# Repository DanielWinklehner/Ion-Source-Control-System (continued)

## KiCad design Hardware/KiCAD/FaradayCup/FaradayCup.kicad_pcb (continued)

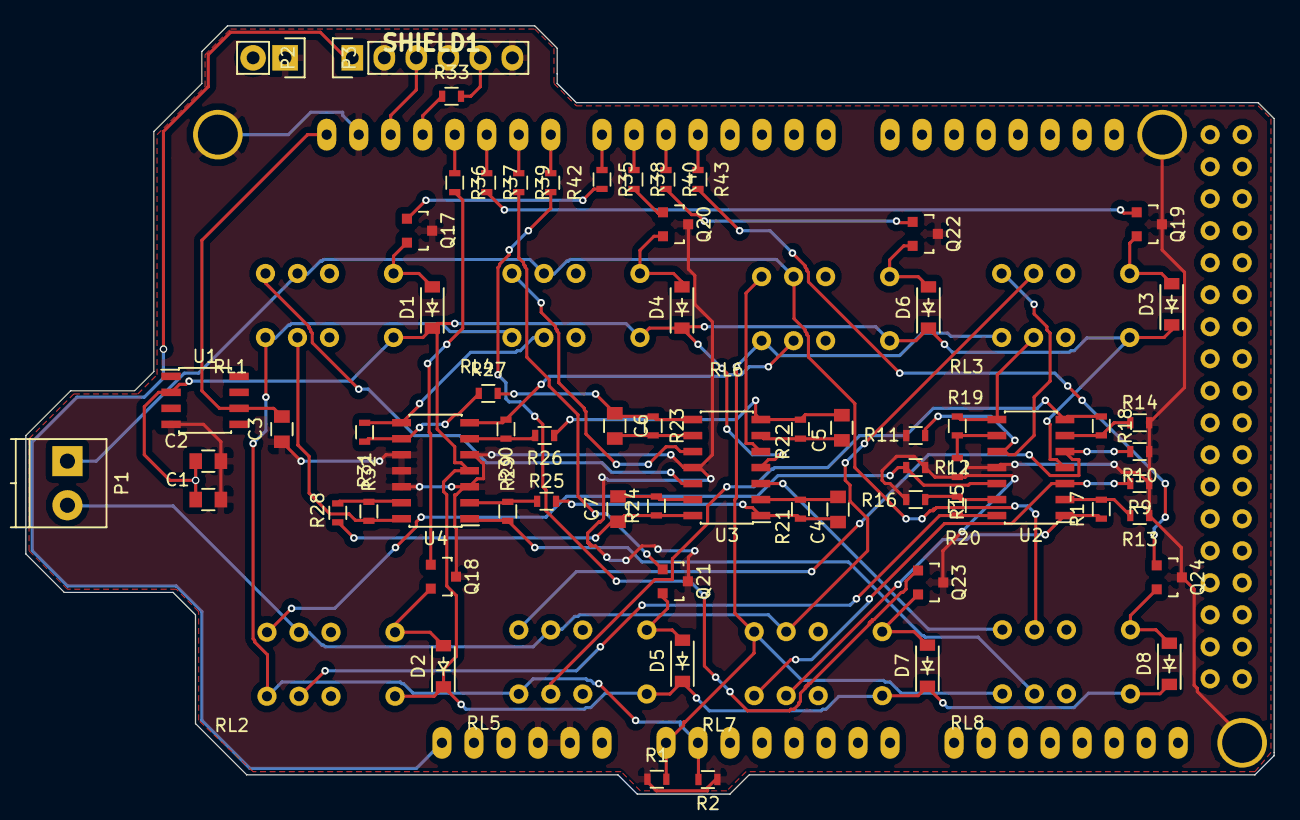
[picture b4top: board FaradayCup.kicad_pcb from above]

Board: 2 copper layers, 99.1 x 61.0 mm, 74 parts (0 on the bottom side), 67 nets.

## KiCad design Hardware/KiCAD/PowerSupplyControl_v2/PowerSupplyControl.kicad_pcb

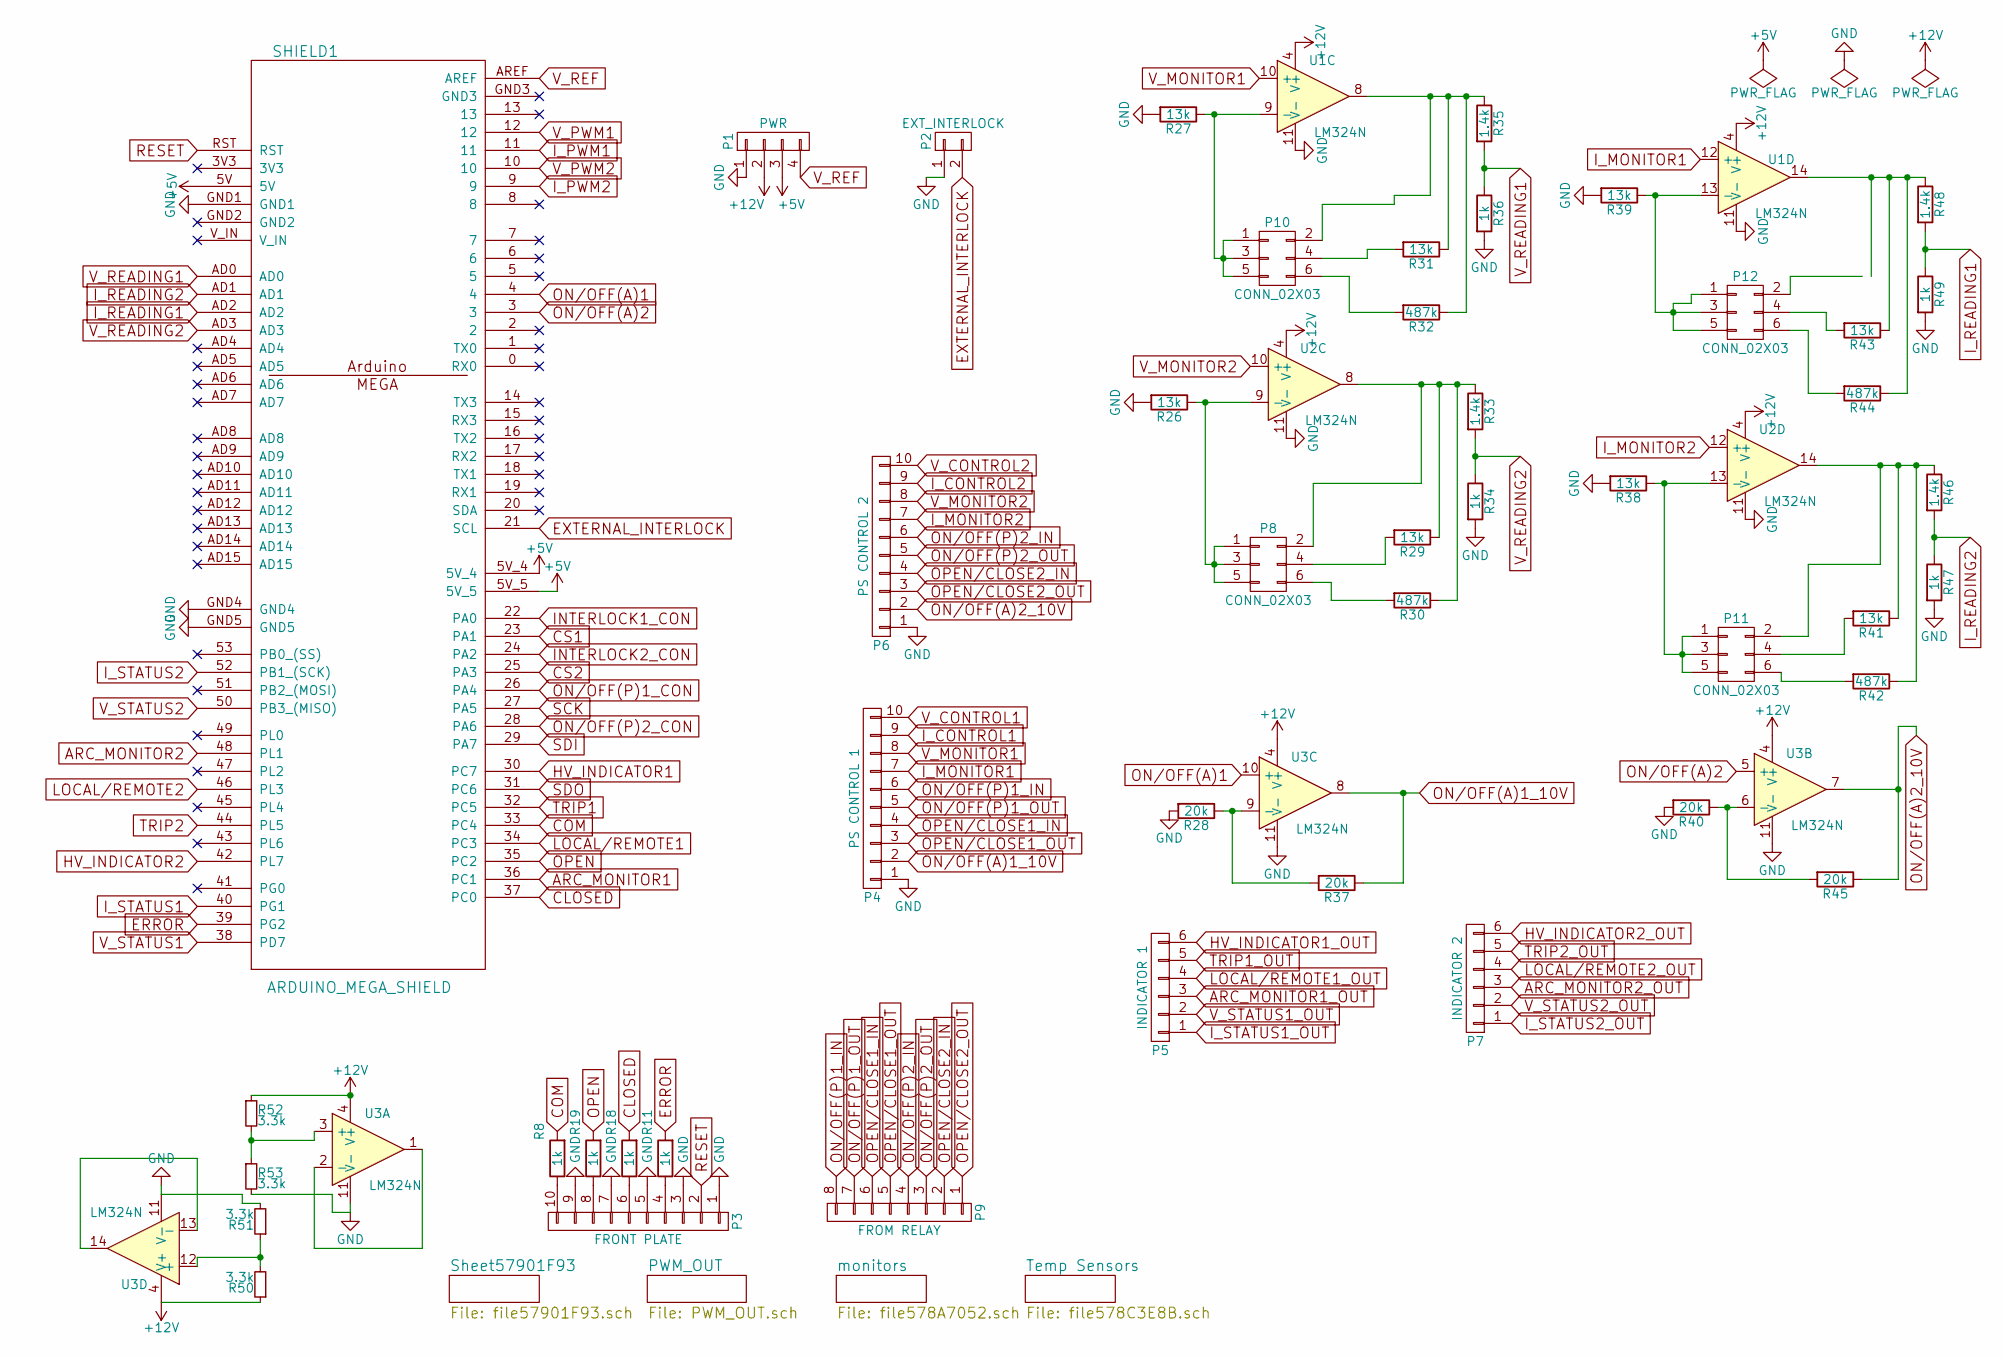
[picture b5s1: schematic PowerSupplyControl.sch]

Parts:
P1: PWR; Pin_Header_Straight_1x04
P2: EXT_INTERLOCK; TerminalBlock_Pheonix_PT-3.5mm_2pol
P3: FRONT PLATE; TerminalBlock_Pheonix_PT-3.5mm_10pol
P4: PS CONTROL 1; TerminalBlock_Pheonix_PT-3.5mm_10pol
P5: INDICATOR 1; Pin_Header_Straight_1x06
P6: PS CONTROL 2; TerminalBlock_Pheonix_PT-3.5mm_10pol
P7: INDICATOR 2; Pin_Header_Straight_1x06
P8, P10, P11, P12: CONN_02X03; Pin_Header_Straight_2x03
P9: FROM RELAY; Pin_Header_Straight_1x08
R8, R11, R18, R19, R34, R36, R47, R49: 1k; R_0603
R26, R27, R29, R31, R38, R39, R41, R43: 13k; R_0603
R28, R37, R40, R45: 20k; R_0603
R30, R32, R42, R44: 487k; R_0805
R33, R35, R46, R48: 1.4k; R_0603
R50, R51, R52, R53: 3.3k; R_0603
SHIELD1: ARDUINO_MEGA_SHIELD
U1, U2, U3: LM324N; SOIC-14_N

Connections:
+5V: P1.3, SHIELD1.5V, SHIELD1.5V_4, SHIELD1.5V_5; also elsewhere on the board
+12V: P1.2, R50.1, R52.1, U1.4 (V+), U2.4 (V+), U3.4 (V+)
ARC_MONITOR1: SHIELD1.36 (PC1); also elsewhere on the board
ARC_MONITOR1_OUT: P5.3; also elsewhere on the board
ARC_MONITOR2: SHIELD1.48 (PL1); also elsewhere on the board
ARC_MONITOR2_OUT: P7.3; also elsewhere on the board
CLOSED: R18.2, SHIELD1.37 (PC0)
COM: R8.2, SHIELD1.33 (PC4)
CS1: SHIELD1.23 (PA1); also elsewhere on the board
CS2: SHIELD1.25 (PA3); also elsewhere on the board
ERROR: R11.2, SHIELD1.39 (PG2)
EXTERNAL_INTERLOCK: P2.2, SHIELD1.21 (SCL)
GND: P1.1, P2.1, P3.1, P3.3, P3.5, P3.7, P3.9, P4.1, P6.1, R26.2, R27.2, R28.2, R34.2, R36.2, R38.2, R39.2, R40.2, R47.2, R49.2, R51.2, R53.2, SHIELD1.GND1, SHIELD1.GND4, SHIELD1.GND5, U1.11 (V-), U2.11 (V-), U3.11 (V-); also elsewhere on the board
HV_INDICATOR1: SHIELD1.30 (PC7); also elsewhere on the board
HV_INDICATOR1_OUT: P5.6; also elsewhere on the board
HV_INDICATOR2: SHIELD1.42 (PL7); also elsewhere on the board
HV_INDICATOR2_OUT: P7.6; also elsewhere on the board
INTERLOCK1_CON: SHIELD1.22 (PA0)
INTERLOCK2_CON: SHIELD1.24 (PA2)
I_CONTROL1: P4.9; also elsewhere on the board
I_CONTROL2: P6.9; also elsewhere on the board
I_MONITOR1: P4.7, U1.12 (+)
I_MONITOR2: P6.7, U2.12 (+)
I_PWM1: SHIELD1.11; also elsewhere on the board
I_PWM2: SHIELD1.9; also elsewhere on the board
I_READING1: R48.2, R49.1, SHIELD1.AD2
I_READING2: R46.2, R47.1, SHIELD1.AD1
I_STATUS1: SHIELD1.40 (PG1); also elsewhere on the board
I_STATUS1_OUT: P5.1; also elsewhere on the board
I_STATUS2: SHIELD1.52 (PB1_(SCK)); also elsewhere on the board
I_STATUS2_OUT: P7.1; also elsewhere on the board
LOCAL/REMOTE1: SHIELD1.34 (PC3); also elsewhere on the board
LOCAL/REMOTE1_OUT: P5.4; also elsewhere on the board
LOCAL/REMOTE2: SHIELD1.46 (PL3); also elsewhere on the board
LOCAL/REMOTE2_OUT: P7.4; also elsewhere on the board
unnamed: P3.4, R11.1
unnamed: P3.6, R18.1
unnamed: P3.8, R19.1
unnamed: P3.10, R8.1
unnamed: P8.1, P8.3, P8.5, R26.1, U2.9 (-)
unnamed: P8.2, R29.1, R30.1, R33.1, U2.8
unnamed: P8.4, R29.2
unnamed: P8.6, R30.2
unnamed: P10.1, P10.3, P10.5, R27.1, U1.9 (-)
unnamed: P10.2, R31.1, R32.1, R35.1, U1.8
unnamed: P10.4, R31.2
unnamed: P10.6, R32.2
unnamed: P11.1, P11.3, P11.5, R38.1, U2.13 (-)
unnamed: P11.2, R41.1, R42.1, R46.1, U2.14
unnamed: P11.4, R41.2
unnamed: P11.6, R42.2
unnamed: P12.1, P12.3, P12.5, R39.1, U1.13 (-)
unnamed: P12.4, R43.2
unnamed: P12.6, R44.2
unnamed: R28.1, R37.2, U3.9 (-)
unnamed: R40.1, R45.2, U3.6 (-)
unnamed: R43.1, R44.1, R48.1, U1.14
unnamed: R50.2, R51.1, U3.12 (+)
unnamed: R52.2, R53.1, U3.3 (+)
unnamed: U3.1, U3.2 (-)
unnamed: U3.13 (-), U3.14
ON/OFF(A)1: SHIELD1.4, U3.10 (+)
ON/OFF(A)1_10V: P4.2, R37.1, U3.8
ON/OFF(A)2: SHIELD1.3, U3.5 (+)
ON/OFF(A)2_10V: P6.2, R45.1, U3.7
ON/OFF(P)1_CON: SHIELD1.26 (PA4)
ON/OFF(P)1_IN: P4.6, P9.8
ON/OFF(P)1_OUT: P4.5, P9.7
ON/OFF(P)2_CON: SHIELD1.28 (PA6)
ON/OFF(P)2_IN: P6.6, P9.4
ON/OFF(P)2_OUT: P6.5, P9.3
OPEN: R19.2, SHIELD1.35 (PC2)
OPEN/CLOSE1_IN: P4.4, P9.6
OPEN/CLOSE1_OUT: P4.3, P9.5
OPEN/CLOSE2_IN: P6.4, P9.2
OPEN/CLOSE2_OUT: P6.3, P9.1
RESET: P3.2, SHIELD1.RST
SCK: SHIELD1.27 (PA5); also elsewhere on the board
SDI: SHIELD1.29 (PA7); also elsewhere on the board
SDO: SHIELD1.31 (PC6); also elsewhere on the board
TRIP1: SHIELD1.32 (PC5); also elsewhere on the board
TRIP1_OUT: P5.5; also elsewhere on the board
TRIP2: SHIELD1.44 (PL5); also elsewhere on the board
TRIP2_OUT: P7.5; also elsewhere on the board
V_CONTROL1: P4.10; also elsewhere on the board
V_CONTROL2: P6.10; also elsewhere on the board
V_MONITOR1: P4.8, U1.10 (+)
V_MONITOR2: P6.8, U2.10 (+)
V_PWM1: SHIELD1.12; also elsewhere on the board
V_PWM2: SHIELD1.10; also elsewhere on the board
V_READING1: R35.2, R36.1, SHIELD1.AD0
V_READING2: R33.2, R34.1, SHIELD1.AD3
V_REF: P1.4, SHIELD1.AREF; also elsewhere on the board
V_STATUS1: SHIELD1.38 (PD7); also elsewhere on the board
V_STATUS1_OUT: P5.2; also elsewhere on the board
V_STATUS2: SHIELD1.50 (PB3_(MISO)); also elsewhere on the board
V_STATUS2_OUT: P7.2; also elsewhere on the board

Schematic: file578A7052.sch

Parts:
R54, R55, R56, R57, R58, R59, R60, R61, R62, R63, R64, R65, R66, R67, R68, R69, R70, R71, R72, R73, R74, R75, R76, R77: 1k; R_0603

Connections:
ARC_MONITOR1: R57.1, R69.2; also elsewhere on the board
ARC_MONITOR1_OUT: R57.2; also elsewhere on the board
ARC_MONITOR2: R63.1, R75.2; also elsewhere on the board
ARC_MONITOR2_OUT: R63.2; also elsewhere on the board
GND: R66.1, R67.1, R68.1, R69.1, R70.1, R71.1, R72.1, R73.1, R74.1, R75.1, R76.1, R77.1; also elsewhere on the board
HV_INDICATOR1: R54.1, R66.2; also elsewhere on the board
HV_INDICATOR1_OUT: R54.2; also elsewhere on the board
HV_INDICATOR2: R60.1, R72.2; also elsewhere on the board
HV_INDICATOR2_OUT: R60.2; also elsewhere on the board
I_STATUS1: R59.1, R71.2; also elsewhere on the board
I_STATUS1_OUT: R59.2; also elsewhere on the board
I_STATUS2: R65.1, R77.2; also elsewhere on the board
I_STATUS2_OUT: R65.2; also elsewhere on the board
LOCAL/REMOTE1: R56.1, R68.2; also elsewhere on the board
LOCAL/REMOTE1_OUT: R56.2; also elsewhere on the board
LOCAL/REMOTE2: R62.1, R74.2; also elsewhere on the board
LOCAL/REMOTE2_OUT: R62.2; also elsewhere on the board
TRIP1: R55.1, R67.2; also elsewhere on the board
TRIP1_OUT: R55.2; also elsewhere on the board
TRIP2: R61.1, R73.2; also elsewhere on the board
TRIP2_OUT: R61.2; also elsewhere on the board
V_STATUS1: R58.1, R70.2; also elsewhere on the board
V_STATUS1_OUT: R58.2; also elsewhere on the board
V_STATUS2: R64.1, R76.2; also elsewhere on the board
V_STATUS2_OUT: R64.2; also elsewhere on the board

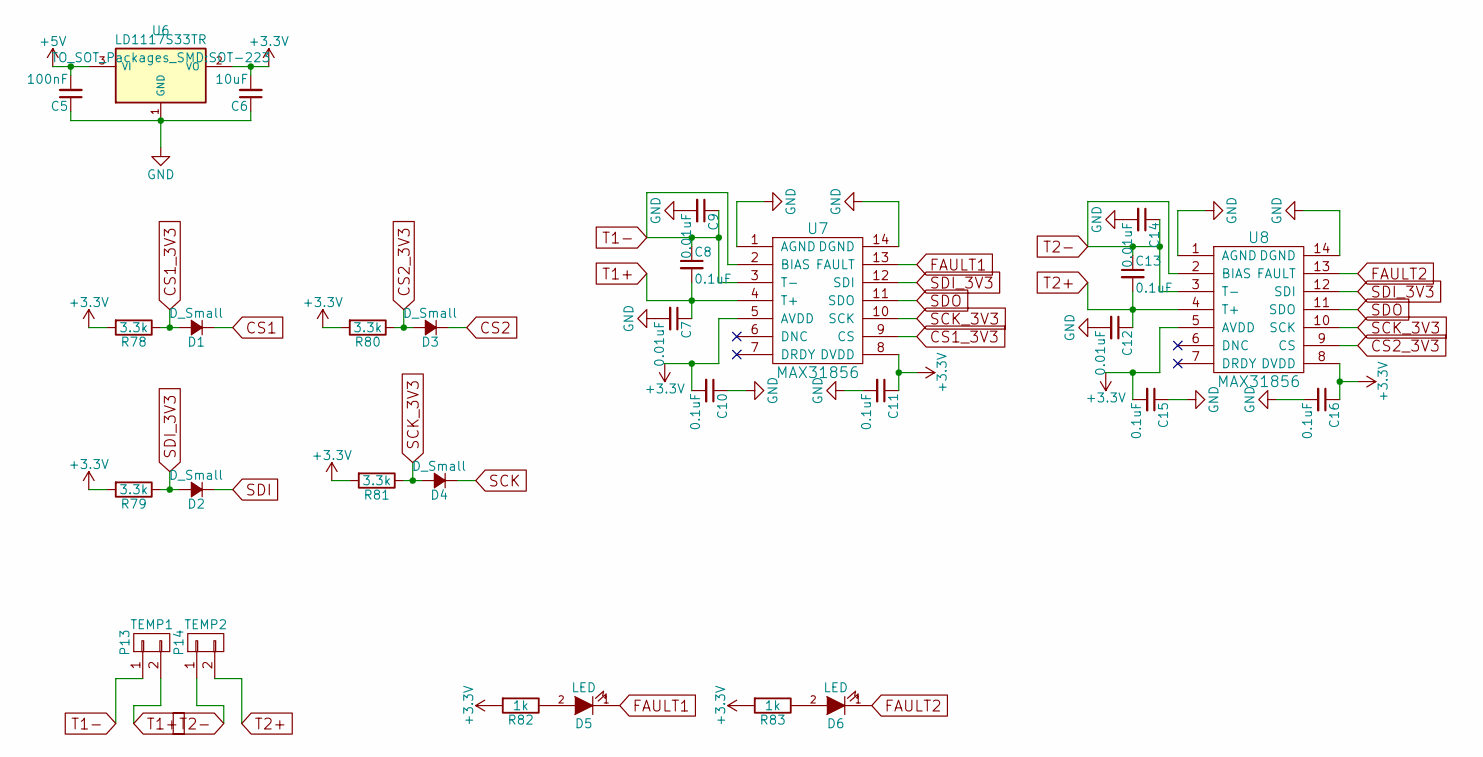
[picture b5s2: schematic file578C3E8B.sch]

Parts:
C5: 100nF; C_0805
C6: 10uF; C_0805
C7, C9, C12, C14: 0.01uF; C_0805
C8, C10, C11, C13, C15, C16: 0.1uF; C_0805
D1, D2, D3, D4: D_Small; SOD-323
D5, D6: LED; LED-3MM
P13: TEMP1; TerminalBlock_Pheonix_PT-3.5mm_2pol
P14: TEMP2; TerminalBlock_Pheonix_PT-3.5mm_2pol
R78, R79, R80, R81: 3.3k; R_0603
R82, R83: 1k; R_0603
U6: LD1117S33TR; SOT-223
U7, U8: MAX31856; TSSOP-14_4.4x5mm_Pitch0.65mm

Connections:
+3V3: C6.2, C10.2, C11.1, C15.2, C16.1, R78.2, R79.2, R80.2, R81.2, R82.2, R83.2, U6.2 (VO), U7.5 (AVDD), U7.8 (DVDD), U8.5 (AVDD), U8.8 (DVDD)
+5V: C5.2, U6.3 (VI); also elsewhere on the board
CS1: D1.1 (K); also elsewhere on the board
CS1_3V3: D1.2 (A), R78.1, U7.9 (CS)
CS2: D3.1 (K); also elsewhere on the board
CS2_3V3: D3.2 (A), R80.1, U8.9 (CS)
FAULT1: D5.1 (K), U7.13 (FAULT)
FAULT2: D6.1 (K), U8.13 (FAULT)
GND: C5.1, C6.1, C7.2, C9.2, C10.1, C11.2, C12.2, C14.2, C15.1, C16.2, U6.1 (GND), U7.1 (AGND), U7.14 (DGND), U8.1 (AGND), U8.14 (DGND); also elsewhere on the board
unnamed: D5.2 (A), R82.1
unnamed: D6.2 (A), R83.1
SCK: D4.1 (K); also elsewhere on the board
SCK_3V3: D4.2 (A), R81.1, U7.10 (SCK), U8.10 (SCK)
SDI: D2.1 (K); also elsewhere on the board
SDI_3V3: D2.2 (A), R79.1, U7.12 (SDI), U8.12 (SDI)
SDO: U7.11 (SDO), U8.11 (SDO); also elsewhere on the board
T1+: C7.1, C8.2, P13.2, U7.4 (T+)
T1-: C8.1, C9.1, P13.1, U7.2 (BIAS), U7.3 (T-)
T2+: C12.1, C13.2, P14.2, U8.4 (T+)
T2-: C13.1, C14.1, P14.1, U8.2 (BIAS), U8.3 (T-)

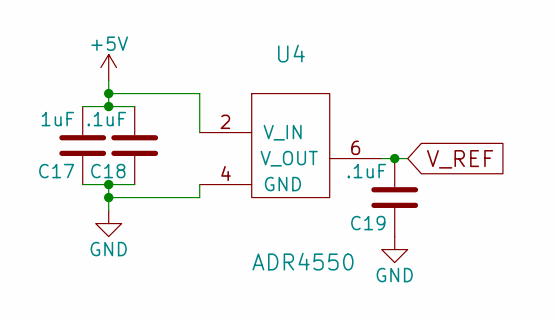
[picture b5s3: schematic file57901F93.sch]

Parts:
C17: 1uF; C_0805
C18, C19: .1uF; C_0805
U4: ADR4550; SOIC-8_3.9x4.9mm_Pitch1.27mm

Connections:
+5V: C17.2, C18.2, U4.2 (V_IN); also elsewhere on the board
GND: C17.1, C18.1, C19.1, U4.4 (GND); also elsewhere on the board
V_REF: C19.2, U4.6 (V_OUT); also elsewhere on the board

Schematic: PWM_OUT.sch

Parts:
C1, C2, C3, C4: 47uF; C_1210
R1, R2, R3, R4: 10k; R_0603
R6, R10, R12, R15, R16, R21, R22, R24: 20k; R_0603
R7, R9, R13, R14, R17, R20, R23, R25: 1k; R_0603
SW1, SW2, SW3, SW4: SPST; SW_DIP_x1_Slide
U1, U2: LM324N; SOIC-14_N

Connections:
+12V: U1.4 (V+), U2.4 (V+); also elsewhere on the board
GND: C1.2, C2.2, C3.2, C4.2, R6.1, R7.2, R14.2, R15.1, R16.1, R17.2, R24.1, R25.2, U1.11 (V-), U2.11 (V-); also elsewhere on the board
I_CONTROL1: R20.1, SW3.1; also elsewhere on the board
I_CONTROL2: R9.1, SW1.1; also elsewhere on the board
I_OUT1: C3.1, R3.1, U1.5 (+)
I_OUT2: C1.1, R1.1, U2.5 (+)
I_PWM1: R3.2; also elsewhere on the board
I_PWM2: R1.2; also elsewhere on the board
unnamed: R7.1, SW1.2
unnamed: R14.1, SW2.2
unnamed: R17.1, SW3.2
unnamed: R25.1, SW4.2
V_CONTROL1: R23.1, SW4.1; also elsewhere on the board
V_CONTROL2: R13.1, SW2.1; also elsewhere on the board
V_OUT1: C2.1, R2.1, U1.3 (+)
V_OUT2: C4.1, R4.1, U2.3 (+)
V_PWM1: R2.2; also elsewhere on the board
V_PWM2: R4.2; also elsewhere on the board

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
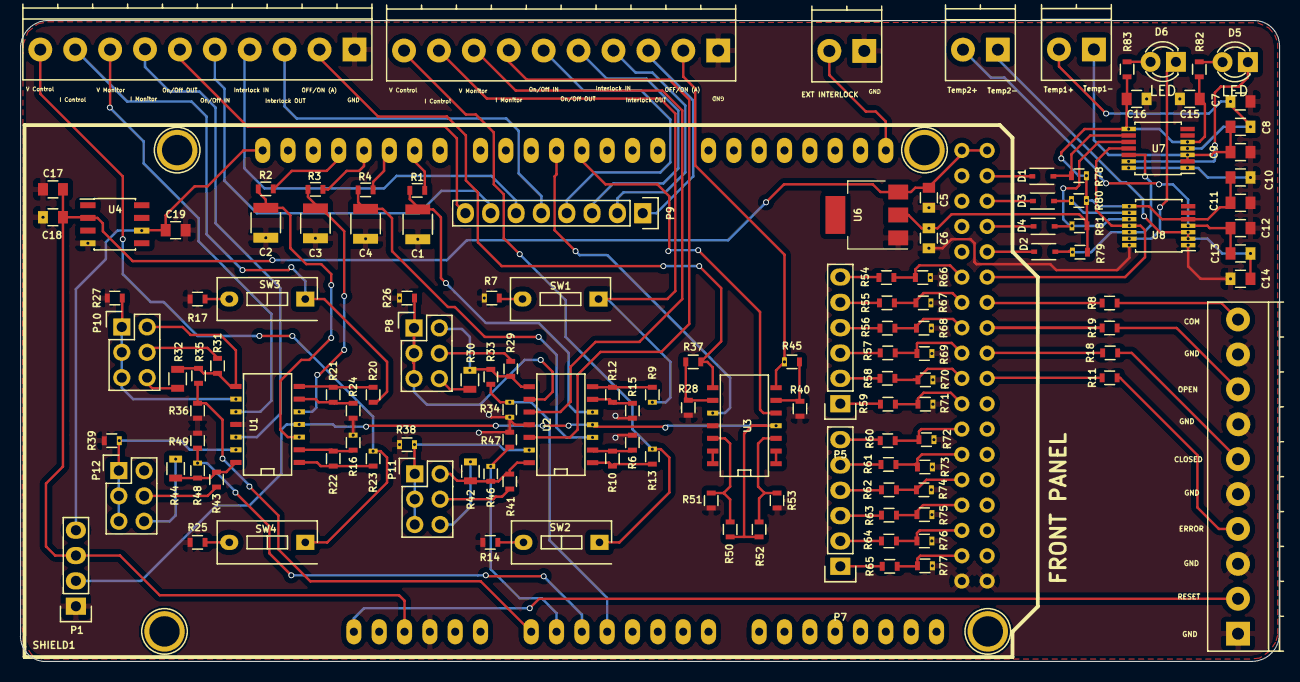
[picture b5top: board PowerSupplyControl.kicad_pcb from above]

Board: 2 copper layers, 126.2 x 64.3 mm, 133 parts (0 on the bottom side), 122 nets.

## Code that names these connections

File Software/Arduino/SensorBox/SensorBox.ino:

#include <Channel.h>
#include <Communication.h>

// Set up serial communication
char inputMessage[128];
mist1::Communication com = mist1::Communication("Sensor Box");

#include <MAX31856.h>

// Flow meters. x5.
const int flowSensorPins[] = {18, 19, 20, 3, 2};
volatile int flowSensorFreqs[] = {0, 0, 0, 0, 0};
float flowSensorFreqsWrite[] = {0.0, 0.0, 0.0, 0.0, 0.0};
unsigned long currentTime;
unsigned long cloopTime;

// Temperature Sensors. 8x.
// The power requirement for the board is less than 2mA.  Most microcontrollers can source or sink a lot more
// than that one each I/O pin.  For example, the ATmega328 supports up to 20mA.  So it is possible to power the
// board using I/O pins for power - so you can turn the board on and off (if you want to).
// FAULT and DRDY are not used by the library (see above)
#define SCK1    44
#define SDI1    42
#define SDO1    40

#define SCK2    49
#define SDI2    51
#define SDO2    53

#define CS1    46
#define CS2    48
#define CS3    50
#define CS4    52
#define CS5    47
#define CS6    45
#define CS7    43
#define CS8    41

// Define pins for error state LED, communication LED
#define LED_ERR 12
#define LED_COM 13

// MAX31856 Initial settings (see MAX31856.h and the MAX31856 datasheet)
// The default noise filter is 60Hz, suitable for the USA
#define CR0_INIT  (CR0_AUTOMATIC_CONVERSION + CR0_OPEN_CIRCUIT_FAULT_TYPE_K /* + CR0_NOISE_FILTER_50HZ */)
#define CR1_INIT  (CR1_AVERAGE_2_SAMPLES + CR1_THERMOCOUPLE_TYPE_K)
#define MASK_INIT (~(MASK_VOLTAGE_UNDER_OVER_FAULT + MASK_THERMOCOUPLE_OPEN_FAULT))

MAX31856 *temperature1;
MAX31856 *temperature2;
MAX31856 *temperature3;
MAX31856 *temperature4;
MAX31856 *temperature5;
MAX31856 *temperature6;
MAX31856 *temperature7;
//MAX31856 *temperature8;

float t[] = {0.0, 0.0, 0.0, 0.0, 0.0, 0.0, 0.0, 0.0};


float get_t1(){
  return t[0];
}

float get_t2(){
  return t[1];
}

float get_t3(){
  return t[2];
}

float get_t4(){
  return t[3];
}

float get_t5(){
  return t[4];
}

float get_t6(){
  return t[5];
}

float get_t7(){
  return t[6];
}

float get_flow1(){
  return flowSensorFreqsWrite[0];
}

float get_flow2(){
  return flowSensorFreqsWrite[1];
}

float get_flow3(){
  return flowSensorFreqsWrite[2];
}

float get_flow4(){
  return flowSensorFreqsWrite[3];
}

float get_flow5(){
  return flowSensorFreqsWrite[4];
}

void dummyFunc(float set_value){
  //Serial.println("Called the dummy function!");
}

void setup()   { 
  // Init Com and Error LED's
  pinMode(LED_ERR, OUTPUT);
  pinMode(LED_COM, OUTPUT);
  digitalWrite(LED_COM, LOW);
  digitalWrite(LED_ERR, LOW);
  
  // Flow Meters.
  for (unsigned i = 0; i < sizeof(flowSensorPins) / sizeof(int); i++) {
    pinMode(flowSensorPins[i], INPUT);
    // Activate the pullup resistor
    digitalWrite(flowSensorPins[i], HIGH);
  }

  Serial.begin(115200); // 115200

  // Interrupts for flow sensors.
  attachInterrupt(digitalPinToInterrupt(flowSensorPins[0]), flow_interrupt0, RISING);
  attachInterrupt(digitalPinToInterrupt(flowSensorPins[1]), flow_interrupt1, RISING);
  attachInterrupt(digitalPinToInterrupt(flowSensorPins[2]), flow_interrupt2, RISING);
  attachInterrupt(digitalPinToInterrupt(flowSensorPins[3]), flow_interrupt3, RISING);
  attachInterrupt(digitalPinToInterrupt(flowSensorPins[4]), flow_interrupt4, RISING);

  // Define the pins used to communicate with the MAX31856
  temperature1 = new MAX31856(SDI1, SDO1, CS1, SCK1);
  temperature2 = new MAX31856(SDI1, SDO1, CS2, SCK1);
  temperature3 = new MAX31856(SDI1, SDO1, CS3, SCK1);
  temperature4 = new MAX31856(SDI1, SDO1, CS4, SCK1);
  temperature5 = new MAX31856(SDI2, SDO2, CS5, SCK2);
  temperature6 = new MAX31856(SDI2, SDO2, CS6, SCK2);
  temperature7 = new MAX31856(SDI2, SDO2, CS7, SCK2);
//  temperature8 = new MAX31856(SDI2, SDO2, CS8, SCK2);
  
  // Initializing the MAX31855's registers
  temperature1->writeRegister(REGISTER_CR0, CR0_INIT);
  temperature1->writeRegister(REGISTER_CR1, CR1_INIT);
  temperature1->writeRegister(REGISTER_MASK, MASK_INIT);

  temperature2->writeRegister(REGISTER_CR0, CR0_INIT);
  temperature2->writeRegister(REGISTER_CR1, CR1_INIT);
  temperature2->writeRegister(REGISTER_MASK, MASK_INIT);

  temperature3->writeRegister(REGISTER_CR0, CR0_INIT);
  temperature3->writeRegister(REGISTER_CR1, CR1_INIT);
  temperature3->writeRegister(REGISTER_MASK, MASK_INIT);

  temperature4->writeRegister(REGISTER_CR0, CR0_INIT);
  temperature4->writeRegister(REGISTER_CR1, CR1_INIT);
  temperature4->writeRegister(REGISTER_MASK, MASK_INIT);

  temperature5->writeRegister(REGISTER_CR0, CR0_INIT);
  temperature5->writeRegister(REGISTER_CR1, CR1_INIT);
  temperature5->writeRegister(REGISTER_MASK, MASK_INIT);

  temperature6->writeRegister(REGISTER_CR0, CR0_INIT);
  temperature6->writeRegister(REGISTER_CR1, CR1_INIT);
  temperature6->writeRegister(REGISTER_MASK, MASK_INIT);

  temperature7->writeRegister(REGISTER_CR0, CR0_INIT);
  temperature7->writeRegister(REGISTER_CR1, CR1_INIT);
  temperature7->writeRegister(REGISTER_MASK, MASK_INIT);

//  temperature8->writeRegister(REGISTER_CR0, CR0_INIT);
//  temperature8->writeRegister(REGISTER_CR1, CR1_INIT);
//  temperature8->writeRegister(REGISTER_MASK, MASK_INIT);

  com.add_channel(mist1::Channel("TEMP1", 't', 1, &dummyFunc, &get_t1));
  com.add_channel(mist1::Channel("TEMP2", 't', 2, &dummyFunc, &get_t2));
  com.add_channel(mist1::Channel("TEMP3", 't', 3, &dummyFunc, &get_t3));
  com.add_channel(mist1::Channel("TEMP4", 't', 4, &dummyFunc, &get_t4));
  com.add_channel(mist1::Channel("TEMP5", 't', 5, &dummyFunc, &get_t5));
  com.add_channel(mist1::Channel("TEMP6", 't', 6, &dummyFunc, &get_t6));
  com.add_channel(mist1::Channel("TEMP7", 't', 7, &dummyFunc, &get_t7));

  com.add_channel(mist1::Channel("FLOW1", 'f', 1, &dummyFunc, &get_flow1));
  com.add_channel(mist1::Channel("FLOW2", 'f', 2, &dummyFunc, &get_flow2));
  com.add_channel(mist1::Channel("FLOW3", 'f', 3, &dummyFunc, &get_flow3));
  com.add_channel(mist1::Channel("FLOW4", 'f', 4, &dummyFunc, &get_flow4));
  com.add_channel(mist1::Channel("FLOW5", 'f', 5, &dummyFunc, &get_flow5));
}

void flow_interrupt0() {
  flowSensorFreqs[0]++;
}

void flow_interrupt1() {
  flowSensorFreqs[1]++;
}

void flow_interrupt2() {
  flowSensorFreqs[2]++;
}

void flow_interrupt3() {
  flowSensorFreqs[3]++;
}

void flow_interrupt4() {
  flowSensorFreqs[4]++;
}

void loop() {
  // Get the current time in milliseconds
  currentTime = millis();
  
  // Every half second, calculate and print litres/hour, and read temperatures
  // The temperatures can be moved into their own if clause to read them 
  // out more often.
  if(currentTime >= (cloopTime + 500)) {
    
    cloopTime = currentTime; // Updates cloopTime
    // Read Flow Meters.
    
    for (unsigned i = 0; i < sizeof(flowSensorPins) / sizeof(int); i++) {
      flowSensorFreqsWrite[i] = (float)flowSensorFreqs[i] * 0.06; //(1000 pulses per l, 60 s in a min, measuring for 0.5 s)
      flowSensorFreqs[i] = 0; // Reset counter.
    }
    // Temperature sensors (read out every half second for now)
    t[0] = temperature1->readThermocouple(CELSIUS);
    t[1] = temperature2->readThermocouple(CELSIUS);
    t[2] = temperature3->readThermocouple(CELSIUS);
    t[3] = temperature4->readThermocouple(CELSIUS);
    t[4] = temperature5->readThermocouple(CELSIUS);
    t[5] = temperature6->readThermocouple(CELSIUS);
    t[6] = temperature7->readThermocouple(CELSIUS);
    // t[7] = temperature8->readThermocouple(CELSIUS);
  }

  // GUI Communication.
  digitalWrite(LED_COM, LOW);

  if (Serial.available() > 0) {
    
    digitalWrite(LED_COM, HIGH);
    
    com.respond_to_input_message();

  }   
}

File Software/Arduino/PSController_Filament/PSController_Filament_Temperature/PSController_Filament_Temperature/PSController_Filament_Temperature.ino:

#include <Channel.h>
#include <Communication.h>
#include <MAX31856.h>

// A PS Controller for the Filament Power Supplies 
// * PS1 = Filament Heating (blue big guy on bottom)
// 0-5 V on Voltage control, 0-100 mV on Current Control
// * PS2 = Filament Discharge (small guy on top)
// 0-10 V on Voltage Control, 0-10 V on Current Control 

// Set up serial communication
char inputMessage[128];
mist1::Communication com = mist1::Communication("TestPSController1");

// Temperature Sensors. 2x.
// The power requirement for the board is less than 2mA.  Most microcontrollers can source or sink a lot more
// than that one each I/O pin.  For example, the ATmega328 supports up to 20mA.  So it is possible to power the
// board using I/O pins for power - so you can turn the board on and off (if you want to).
// FAULT and DRDY are not used by the library (see above)
#define SCK 27
#define SDI 29
#define SDO 31
#define CS1 23
#define CS2 25

// MAX31856 Initial settings (see MAX31856.h and the MAX31856 datasheet)
// The default noise filter is 60Hz, suitable for the USA
#define CR0_INIT  (CR0_AUTOMATIC_CONVERSION + CR0_OPEN_CIRCUIT_FAULT_TYPE_K /* + CR0_NOISE_FILTER_50HZ */)
#define CR1_INIT  (CR1_AVERAGE_2_SAMPLES + CR1_THERMOCOUPLE_TYPE_K)
#define MASK_INIT (~(MASK_VOLTAGE_UNDER_OVER_FAULT + MASK_THERMOCOUPLE_OPEN_FAULT))

// Define pins for error state LED, communication LED
#define LED_ERR 39
#define LED_COM 33
#define LED_OPEN 35
#define LED_CLOSED 37

MAX31856 *temperature1;
MAX31856 *temperature2;

// float t[] = {0.0, 0.0};

// Define pins for power supply control voltages
#define PS1_V_OUT 12  // Cave: For Timer1, "2" maps to pin 12
#define PS1_I_OUT 11  // Cave: For Timer1, "1" maps to pin 11
#define PS2_V_OUT 10
#define PS2_I_OUT 9

// Define pins for power supply read voltages
#define PS1_V_IN 0
#define PS1_I_IN 2
#define PS2_V_IN 3
#define PS2_I_IN 1

// Define pins for relays (PS on/off, PS interlock)
#define PS1_ON 14
#define PS1_ILK 15
#define PS2_ON 16
#define PS2_ILK 17

//Define External Interlock Pin
#define EXT_ILK 21

//Define interlock open/closed
#define CLOSED 1
#define OPEN 0

// Set up interlock switch debounce time
long debouncing_time = 150; //Debouncing Time in Milliseconds
volatile unsigned long last_micros;

volatile unsigned int error_state = 0;
volatile unsigned int interlock_state = OPEN;

/*
// function object prototype for setting relay state
typedef struct setRelay {
 // constructor
 setRelay (const uint8_t relay) : relay_ (relay) {}
 // operator ()
 void operator () (int state)
   {
     if (state == 1) {
       digitalWrite(relay_, LOW);
     } else if (state == 0) {
       digitalWrite(relay_, HIGH);
     }
   }  // end of operator ()

 private:    
   uint8_t relay_;
};

setRelay set_relay1 (RELAY1);
setRelay set_relay2 (RELAY2);
setRelay set_relay3 (RELAY3);
setRelay set_relay4 (RELAY4);
*/

float get_t1(){
  // return t[0];
  return temperature1->readThermocouple(CELSIUS);
}

float get_t2(){
  // return t[1];
  return temperature2->readThermocouple(CELSIUS);
}

void set_ps1_on (float state){
  if (state == 1.0) {
    digitalWrite(PS1_ON, LOW);
  } else if (state == 0.0) {
    digitalWrite(PS1_ON, HIGH);
  }
}

void set_ps2_on (float state){
  if (state == 1.0) {
    digitalWrite(PS2_ON, LOW);
  } else if (state == 0.0) {
    digitalWrite(PS2_ON, HIGH);
  }
}

void set_ps1_v (float value){
  value *= 48.2;
  analogWrite(PS1_V_OUT, value);
}

float get_ps1_v (){
  analogRead(PS1_V_IN);
  int sum10 = 0;
  for (int i = 0; i < 10; i++){
    sum10 += analogRead(PS1_V_IN);
  }
  return sum10 / 1605.4;
}

void set_ps2_v (float value){
  value *= 24.1;
  analogWrite(PS2_V_OUT, value);
}

float get_ps2_v (){
  analogRead(PS2_V_IN);
  int sum10 = 0;
  for (int i = 0; i < 10; i++){
    sum10 += analogRead(PS2_V_IN);
  }
  return sum10 / 852.7;
}

void set_ps1_i (float value){
  value *= 48.2;
  analogWrite(PS1_I_OUT, value);
}

float get_ps1_i (){
  analogRead(PS1_I_IN);
  int sum10 = 0;
  for (int i = 0; i < 10; i++){
    sum10 += analogRead(PS1_I_IN);
  }
  return sum10 / 10.0;
}

void set_ps2_i (float value){
  value *= 24.1;
  analogWrite(PS2_I_OUT, value);
}

float get_ps2_i (){
  analogRead(PS2_I_IN);
  int sum10 = 0;
  for (int i = 0; i < 10; i++){
    sum10 += analogRead(PS2_I_IN);
  }
  return sum10 / 852.7;
}

float get_ext_ilk(){
  return (float) interlock_state;
}

void dummySetFunc(float set_value){
  //Serial.println("Called the dummy function!");
}

float dummyGetFunc(){
  //Serial.println("Called the dummy function!");
}

void setup() {
  Serial.begin(115200);

  //delay(10);

  // Set up analog reference
  analogReference(EXTERNAL);
  
  // Define the pins used to communicate with the MAX31856
  temperature1 = new MAX31856(SDI, SDO, CS1, SCK);
  temperature2 = new MAX31856(SDI, SDO, CS2, SCK);
  
  // Initializing the MAX31855's registers
  temperature1->writeRegister(REGISTER_CR0, CR0_INIT);
  temperature1->writeRegister(REGISTER_CR1, CR1_INIT);
  temperature1->writeRegister(REGISTER_MASK, MASK_INIT);

  temperature2->writeRegister(REGISTER_CR0, CR0_INIT);
  temperature2->writeRegister(REGISTER_CR1, CR1_INIT);
  temperature2->writeRegister(REGISTER_MASK, MASK_INIT);

  // Initialize Com and Error LED's
  pinMode(LED_ERR, OUTPUT);
  pinMode(LED_COM, OUTPUT);
  pinMode(LED_OPEN, OUTPUT);
  pinMode(LED_CLOSED, OUTPUT);
  
  digitalWrite(LED_COM, LOW);
  digitalWrite(LED_ERR, LOW);
  digitalWrite(LED_OPEN, LOW);
  digitalWrite(LED_CLOSED, LOW);

  // Init V and I output PWM's
  pinMode(PS1_V_OUT, OUTPUT);
  pinMode(PS1_I_OUT, OUTPUT);
  pinMode(PS2_V_OUT, OUTPUT);
  pinMode(PS2_I_OUT, OUTPUT);

  // Set them to 0 V
  digitalWrite(PS1_V_OUT, LOW);
  digitalWrite(PS1_I_OUT, LOW);
  digitalWrite(PS2_V_OUT, LOW);
  digitalWrite(PS2_I_OUT, LOW);

  // Init Relay pins
  pinMode(PS1_ON, OUTPUT);
  pinMode(PS2_ON, OUTPUT);
  pinMode(PS1_ILK, OUTPUT);
  pinMode(PS2_ILK, OUTPUT);

  // Set them all to OFF (pulled HIGH)
  digitalWrite(PS1_ON, HIGH);
  digitalWrite(PS2_ON, HIGH);
  digitalWrite(PS1_ILK, HIGH);
  digitalWrite(PS2_ILK, HIGH);

  // Init External Interlock Pin
  pinMode(EXT_ILK, INPUT);

  com.add_channel(mist1::Channel("TEMP1", 't', 1, &dummySetFunc, &get_t1));
  com.add_channel(mist1::Channel("TEMP2", 't', 2, &dummySetFunc, &get_t2));
  com.add_channel(mist1::Channel("FIL_CUR_ON", 'o', 1, &set_ps1_on, &dummyGetFunc));
  com.add_channel(mist1::Channel("FIL_DCHRG_ON", 'o', 2, &set_ps2_on, &dummyGetFunc));
  com.add_channel(mist1::Channel("FIL_CUR_V", 'v', 1, &set_ps1_v, &get_ps1_v));
  com.add_channel(mist1::Channel("FIL_DCHRG_V", 'v', 2, &set_ps2_v, &get_ps2_v));
  com.add_channel(mist1::Channel("FIL_CUR_I", 'i', 1, &set_ps1_i, &get_ps1_i));
  com.add_channel(mist1::Channel("FIL_DCHRG_I", 'i', 2, &set_ps2_i, &get_ps2_i));
  com.add_channel(mist1::Channel("EXT_ILK", 'x', 1, &dummySetFunc, &get_ext_ilk));  //To read interlock status
  
}

void loop() {
  // Read out temperature sensors
  // t[0] = temperature1->readThermocouple(CELSIUS);
  // t[1] = temperature2->readThermocouple(CELSIUS);

  if (digitalRead(EXT_ILK) == HIGH){
    digitalWrite(PS1_ILK, HIGH);
    digitalWrite(PS2_ILK, HIGH);
    digitalWrite(LED_CLOSED, LOW);
    digitalWrite(LED_OPEN, HIGH);
    interlock_state = OPEN;
  } else {
    digitalWrite(PS1_ILK, LOW);
    digitalWrite(PS2_ILK, LOW);
    digitalWrite(LED_CLOSED, HIGH);
    digitalWrite(LED_OPEN, LOW);
    interlock_state = CLOSED;
  }

  // GUI Communication.
  digitalWrite(LED_COM, LOW);

  if (Serial.available()) {
    
    digitalWrite(LED_COM, HIGH);
    
    com.respond_to_input_message();

  }  
}

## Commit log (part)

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2016-05-31 Read in values from arduino
2016-05-31 Set values
2016-05-31 Code comments.
2016-05-31 Arduino code cleanup
2016-06-01 gitignore
2016-06-01 Separate Interlock System into two devices
2016-06-02 Revamp: move device detials from Handler to Device / Channel
2016-06-06 06/06/2016 backup
2016-06-06 Only the main thread updates the GUI
2016-06-06 Data logging h5py initalization
2016-06-06 Set value
2016-06-06 Setting value
2016-06-06 Setting works
2016-06-06 Setting works + Widget ordering
2016-06-06 Arduino code => Arrays
2016-06-07 All channels for interlock box
2016-06-07 Logging
2016-06-09 Stuff
2016-06-10 Setting / reading both resume
2016-06-10 Device locks when corresponding arduino is unplugged and unlocks when it's plugged back in.
2016-06-20 File handling JSON
2016-06-20 Device add multiple widget fix
2016-06-20 Select which devices to save.
2016-06-21 Add channel / device manually
2016-06-21 Tree View on Settings Page
2016-06-21 Tree View + Expand All / Collapse All buttons
2016-06-22 Add / Edit device / channel
2016-06-22 Adding channel works
2016-06-27 Adding devices adds the device to tree view too
2016-06-27 Procedures
2016-06-27 Arbitrary functions as actions for procedures.
2016-06-28 Plotting:
2016-06-30 Plotting
2016-07-01 Multiple plot windows proper arrangement
2016-07-01 Arrangement on removal also works
2016-07-27 Arduino communication char array
2016-07-27 Ardduino
2016-07-28 Arduino number format
2016-07-28 Server code to send / parse messages to arduino
2016-07-29 Server => Client moved to ./GUI/
2016-07-29 HTTP Server
2016-07-29 Server checking for alive
2016-08-01 server ip
2016-08-02 WSGI
2016-08-02 server mrver messages
2016-08-03 server set values + fixed plotting speed
2016-08-05 server DB
2016-08-09 Server Display
2016-08-15 Stugff
2016-08-15 server pool
2016-08-16 server pool port open one per device
2016-08-17 serv
2016-09-04 removed pi backup
2016-09-04 readme
2016-12-08 Arduino com library
2016-12-08 Renamed server directory
2017-01-11 New Arduino code
2017-01-12 Moved old arduino code
2017-01-13 Rearrange + dummy server
2017-01-13 Dummy server- responds with channel name
2017-01-13 removed pyc files
2017-01-13 More folder reorganization
2017-01-13 hardware and documents included
2017-01-13 Moved todo
2017-01-13 changed .gitignore
2017-01-13 File renamings
2017-01-13 merged
2017-01-13 More renaming:
2017-01-13 refactoring
2017-01-13 Dummy server correct precision
2017-01-13 Server cleanup + setup
2017-01-13 minor bugs
2017-01-18 Reformatted MFCDriver.py
2017-01-18 Server responds to query messages- change needed because of changes to Arduino code
2017-01-18 server splits message now
2017-01-18 Server handles error messages from the Arduino
2017-01-19 Correct number of Precisions
2017-01-19 Changed file name to remove spaces
2017-01-22 Changed some command names to remove ambiguity, and parse message now displays error message
2017-01-24 Dummy server fix + Gunicorn setup
2017-01-24 Dummy server works ~18Hz
2017-01-25 getting to latest master...
2017-01-25 Message formats
2017-01-25 Working version of Server
2017-01-25 Worked on first driver response to server
2017-01-25 ThreadPool no longer specifies no. of threads to use- so uses one per each item in the iterator
2017-01-30 cosmetics -DW
2017-01-30 worked on driver responses
2017-01-31 Moved ThreadPool to global, increased polling rate to 80 Hz. Fixed rounding to full seconds in DummyServer to get nice sine wave. -DW
2017-01-31 reverted and changed a few details in DummyServer. always use /kill so threads are properly terminated. Noticed that we can stably go above 40 Hz after reboot of PC, but drops down after a while (~10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
2017-02-01 worked on driver
2017-02-01 Minor changes -DW
2017-02-01 Made classes for MFCDriver
2017-02-01 More minor changes -DW
2017-02-01 DummyServer uses Device Drivers now
2017-02-01 touched up the class in MFCDriver
2017-02-01 some more clean up
2017-02-02 Location of Driver
2017-02-02 Cleaned up DummyServer
2017-02-02 changed arduino/ to device/ again -DW
2017-02-02 New Raspiserver works
2017-02-02 RasPiServer works
2017-02-02 process/thread implementation for query -DW
2017-02-02 Started implementing GObject Signal based sending of values to server. -DW
2017-02-03 More work on setting values, added check for non-float or invalid (outside limits) entries. -DW
2017-02-03 Added global polling rate and disabled device polling rate until we implement getting it from server. -DW
2017-02-08 Added the modified / debugged server code to RasPiServer/
2017-02-09 added modified IonGaugeController Arduino code. Only read back pressure as of now. -DW
2017-02-10 Setting up for use at PSFC. -DW
2017-02-14 Set channel value method
2017-02-15 Rewrote the RasPi server, more lightweight, now uses a process to keep ports/device ID's updated. Needs to be able to look for MFC at serial port. Do that over at PSFC where I can connect the MFC. -DW
2017-02-15 Intermediate stage of rewriting the server. For reference only, DO NOT USE. -DW
2017-02-15 Some small changes in the Main GUI file also -DW
2017-02-15 Arduino changes. Mainly I reduced the delay in getting serial data from 5 ms to 100 us to get better polling rate. -DW
2017-02-15 tiny change. -DW
2017-02-20 Added Arduino code for the specific PS controllers (HV and Filament), set up the GUI to run these at PSFC. -DW
2017-02-20 updated to be in same state as actual server on RasPi after I made local changes. -DW
2017-02-20 Started implementing the MFC device. -DW
2017-02-21 Latest at PSFC. -DW
2017-02-22 Fixed having read/write channels ("both"), improved my previous fix for RS485 and separate baud rates. -DW
2017-02-23 Added temp sensors to Filament PS Controller Arduino software. -DW
2017-08-08 general log directory creation
2017-08-09 working on new features
2017-08-10 Working for Python 3
2017-08-10 added list of required packages
2017-08-10 plotting works in py3/gtk3
2017-08-10 added working pyqtgraph example
2017-08-11 set up qt version
2017-08-15 added several event handlers
2017-08-17 plotting works
2017-08-18 fixed server bug, gui doesn't crash when device unplugged
2017-08-18 small changes & started working on procedures
2017-08-19 working on procedures
2017-08-20 procedures work in the ui
2017-08-20 organizing
2017-08-20 removed old file
2017-08-20 Working on device page
2017-08-24 working on settings page
2017-08-25 reorganizing, use previous commit for working features
2017-08-25 still rearranging, this commit has broken features
2017-08-25 plotting mostly working again
2017-08-25 test commit
2017-08-25 test
2017-08-26 small fixes
2017-08-26 I think all features are working again
2017-08-26 Added error dialogs, bug fixes
2017-08-27 export to json works, added some icons
2017-08-28 saving/loading from json works, start/pause/stop functional
2017-08-28 error handling, bug fixes
2017-08-28 more error handling
2017-08-29 added tdk driver, bug fixes
2017-08-29 quick fix to check for extension when saving devices
2017-08-30 Fixed serial com error -DW
2017-08-30 removed junk files
2017-08-30 removed a print statement -DW
2017-08-30 revised device/channel editing
2017-08-30 clean up code
2017-08-30 made settings page code more modular
2017-08-30 fixed display formatting bug
2017-08-30 channels save scaling and display mode info
2017-08-30 plot settings dialog in the works
2017-08-31 plots have time axes
2017-08-31 plot settings dialog added
2017-08-31 saving/loading plot settings seems to work
2017-08-31 pinned plot now updates with plot settings
2017-09-01 made plot widget with date axis its own class
2017-09-01 fixed a few bugs, window close button now kills threads
2017-09-01 moved validation logic to main window class
2017-09-01 expanding procedure dialog
2017-09-05 fixed set value bug, added pipe message queue
2017-09-05 save as button
2017-09-05 latest
2017-09-05 fixed channel editing bug
2017-09-05 loading now sets save directory
2017-09-05 testing prolific driver
2017-09-05 rekdriver
2017-09-05 fixed channel creation bug
2017-09-05 fixed bug
2017-09-05 fixed some lag issues -DW
2017-09-06 DONT PULL -- reworking settings page in progress
2017-09-06 DONT PULL -- still working on revising settings
2017-09-07 almost done reworking settings page
2017-09-07 pull this version -- many bug fixes
2017-09-07 number of stored points is user-editable
2017-09-07 deques retain values when number of points change
2017-09-07 working on pid procedures
2017-09-08 working on new procedure features
2017-09-08 pid beta
2017-09-08 fixed small bug with procedures and statuses
2017-09-09 can now save/load pid procedures and some settings
2017-09-10 preparing to delete devices/channels
2017-09-10 changed strings/variable names
2017-09-11 reorder devices on overview
2017-09-11 fixed some delayed entry form updates, ignorable warning dialog added
2017-09-11 added saving splitter settings, removed prints, only one warning
2017-09-11 can now delete devices/channels
2017-09-11 fixed lingering entry form bug
2017-09-11 added styles, fixed floating entry forms
2017-09-11 slight tweaks to style sheet
2017-09-11 style changes, color dialog fix
2017-09-12 fixed load error -TW
2017-09-12 fixed issue where pid editing would not show correct channels
2017-09-13 added delay, averaging and offset to pid
2017-09-13 pid averaging
2017-09-13 change pid target while running
2017-09-14 working on timer procedures
2017-09-14 working on timer procedure
2017-09-15 added custom widget for device/channel selection
2017-09-15 setting up for using new widget
2017-09-15 using new widget to clean up code
2017-09-15 procedure dialog uses new widget
2017-09-15 cleaning up
2017-09-15 added teensy pinout
2017-09-15 fixed timing procedure missing function -TW
2017-09-27 dials added to channels
2017-09-27 dials have steps equal to 10^precision
2017-10-16 device timeout and retrying prototype
2017-10-18 move device widget into separate class
2017-10-18 timeout counters for error devices working
2017-10-18 device retry creates only one thread instead of two
2017-10-23 dials now block mouse events
2017-10-23 fixes I hope
2017-10-27 moved channel widget to separate class
2017-10-27 can update channel display mode without restarting
2017-10-30 initial test commit
2017-11-02 set dials via text box
2017-11-06 working on kicad now
2017-11-07 prettier html page for raspi server
2017-11-07 oops
2017-11-08 added style sheet for table display
2017-11-08 device retry timers are synced to global 30 seconds
2017-11-08 force retry connection button
2017-11-08 added channel column to server webpage
2017-11-08 last commit before merge
2017-11-09 fixed keyerror on htmlpage -TW
2017-11-09 fixed dial decorator error -TW
2017-11-09 untested bug fixes, things might crash
2017-11-09 organized. pids can pause
2017-11-10 fixed typos
2017-11-10 fixing channel dials
2017-11-10 dial updates on channel edits
2017-11-16 working on temp sensors
2017-11-21 pid sets only between limits
2017-12-05 moving loading/saving to separate file
2017-12-13 scanner daq, temp sensor update
2017-12-13 test ltest layouayout
2017-12-13 added gerber files
2017-12-13 updated pico programs
2018-01-10 Added stepper motor documentation and drivers
2018-01-11 added drill file
2018-01-12 fixed file load error -TW
2018-01-29 starting stepper motor controller class
2018-01-29 added NI-6001 Manual -DW
2018-02-02 working on scannerdaq
2018-02-16 tweak to ion gauge controller -DW
2018-02-16 Added Teensy code for ion gauge controller -DW
2018-02-22 updating temperature sensor part list & software
2018-02-22 updated parts list with arduino-compatible barrel jack
2018-03-23 Teensy based ion gauge controller and Matsusada CO documentation added -DW
2018-03-28 adding experimental RasPiServer_v4
2018-04-03 Matsusada driver now working with newest raspi server, but communication still slow
2018-04-09 working on async raspi server
2018-04-09 update control system to work with async raspi server
2018-04-09 fix server hang on thread start bug
2018-04-09 small fix to underscore device ids
2018-04-09 add per-device polling rates
